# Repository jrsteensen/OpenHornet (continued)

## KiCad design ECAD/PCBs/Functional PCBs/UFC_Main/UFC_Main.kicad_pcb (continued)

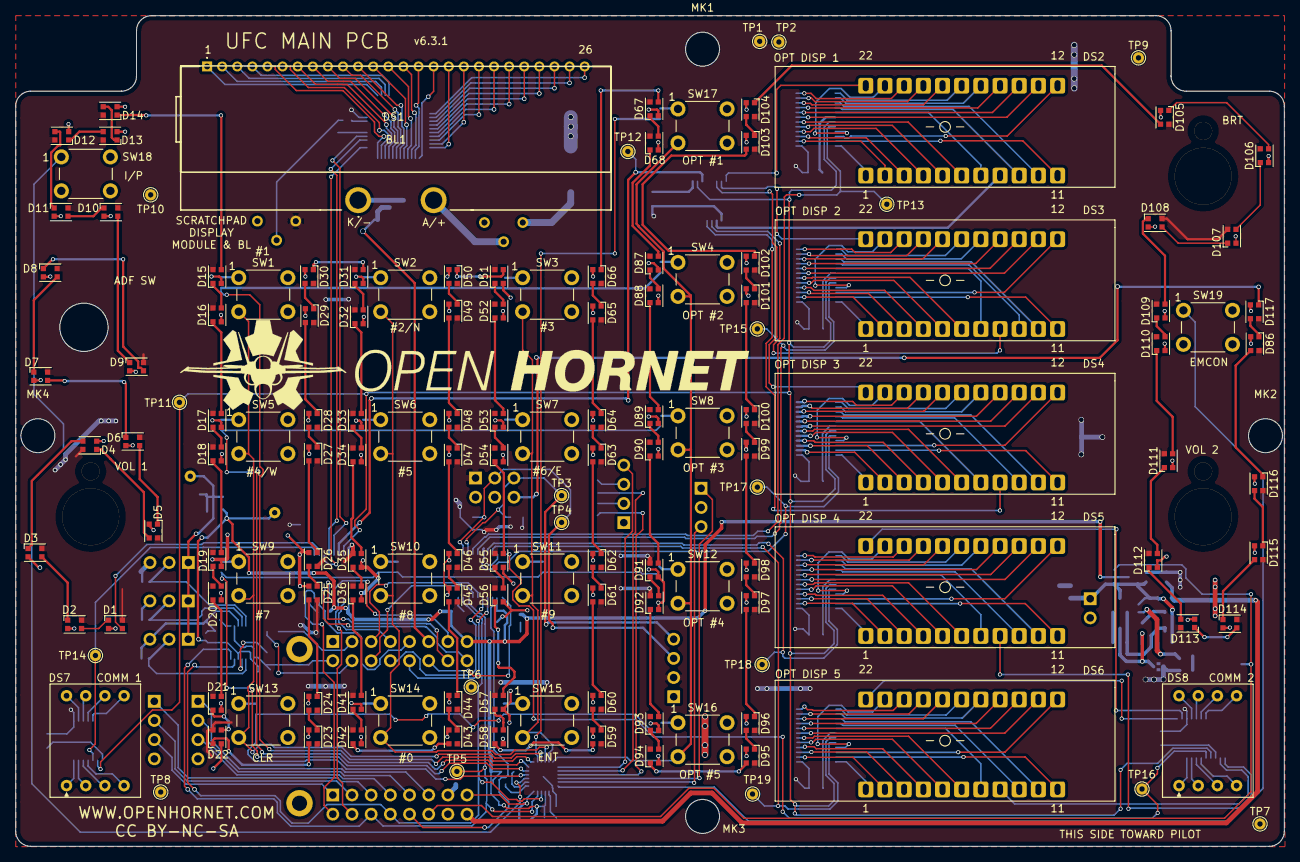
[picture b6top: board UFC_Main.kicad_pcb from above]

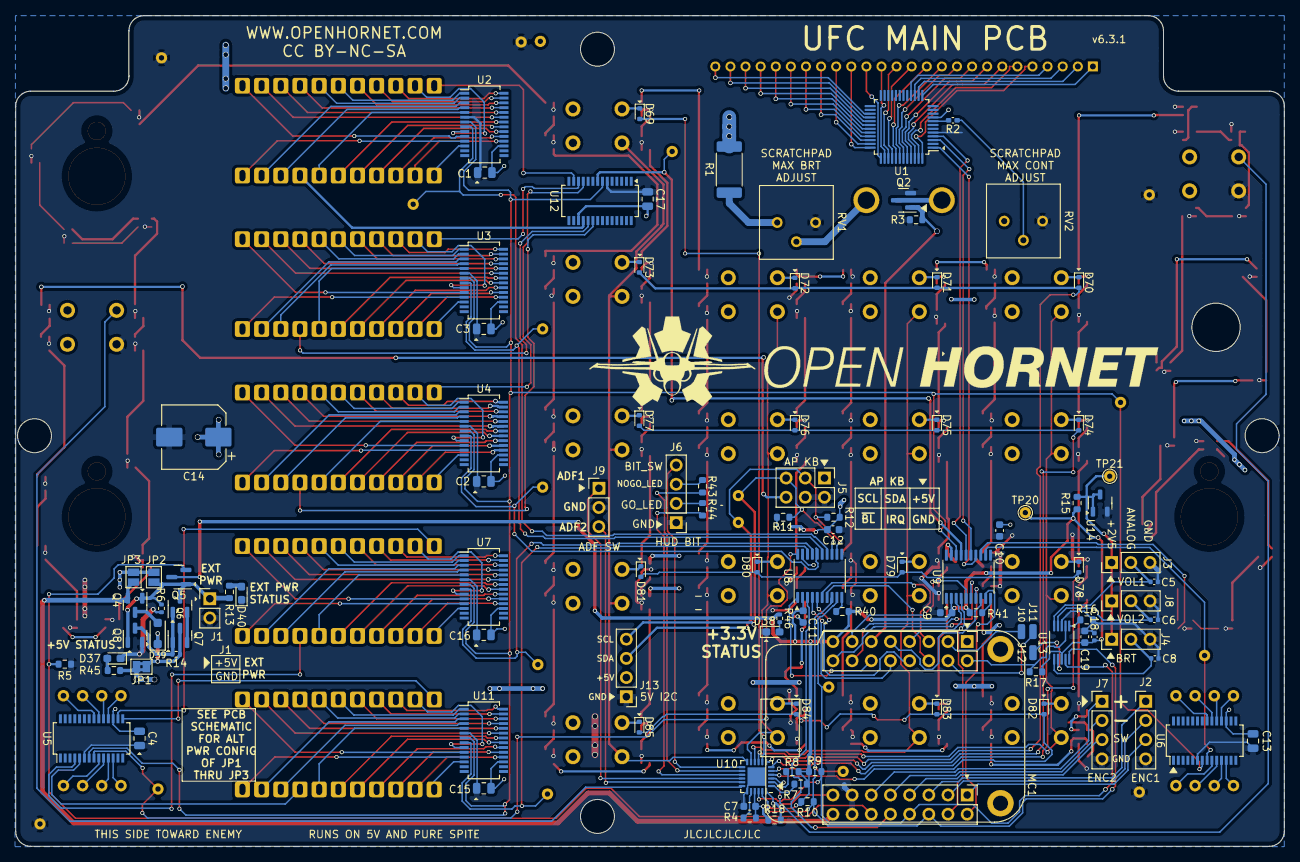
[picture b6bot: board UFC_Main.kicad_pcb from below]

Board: 2 copper layers, 168.0 x 110.0 mm, 257 parts (105 on the bottom side), 353 nets.

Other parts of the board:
LOGO: LOGO; LOGO_OH_Text_Large

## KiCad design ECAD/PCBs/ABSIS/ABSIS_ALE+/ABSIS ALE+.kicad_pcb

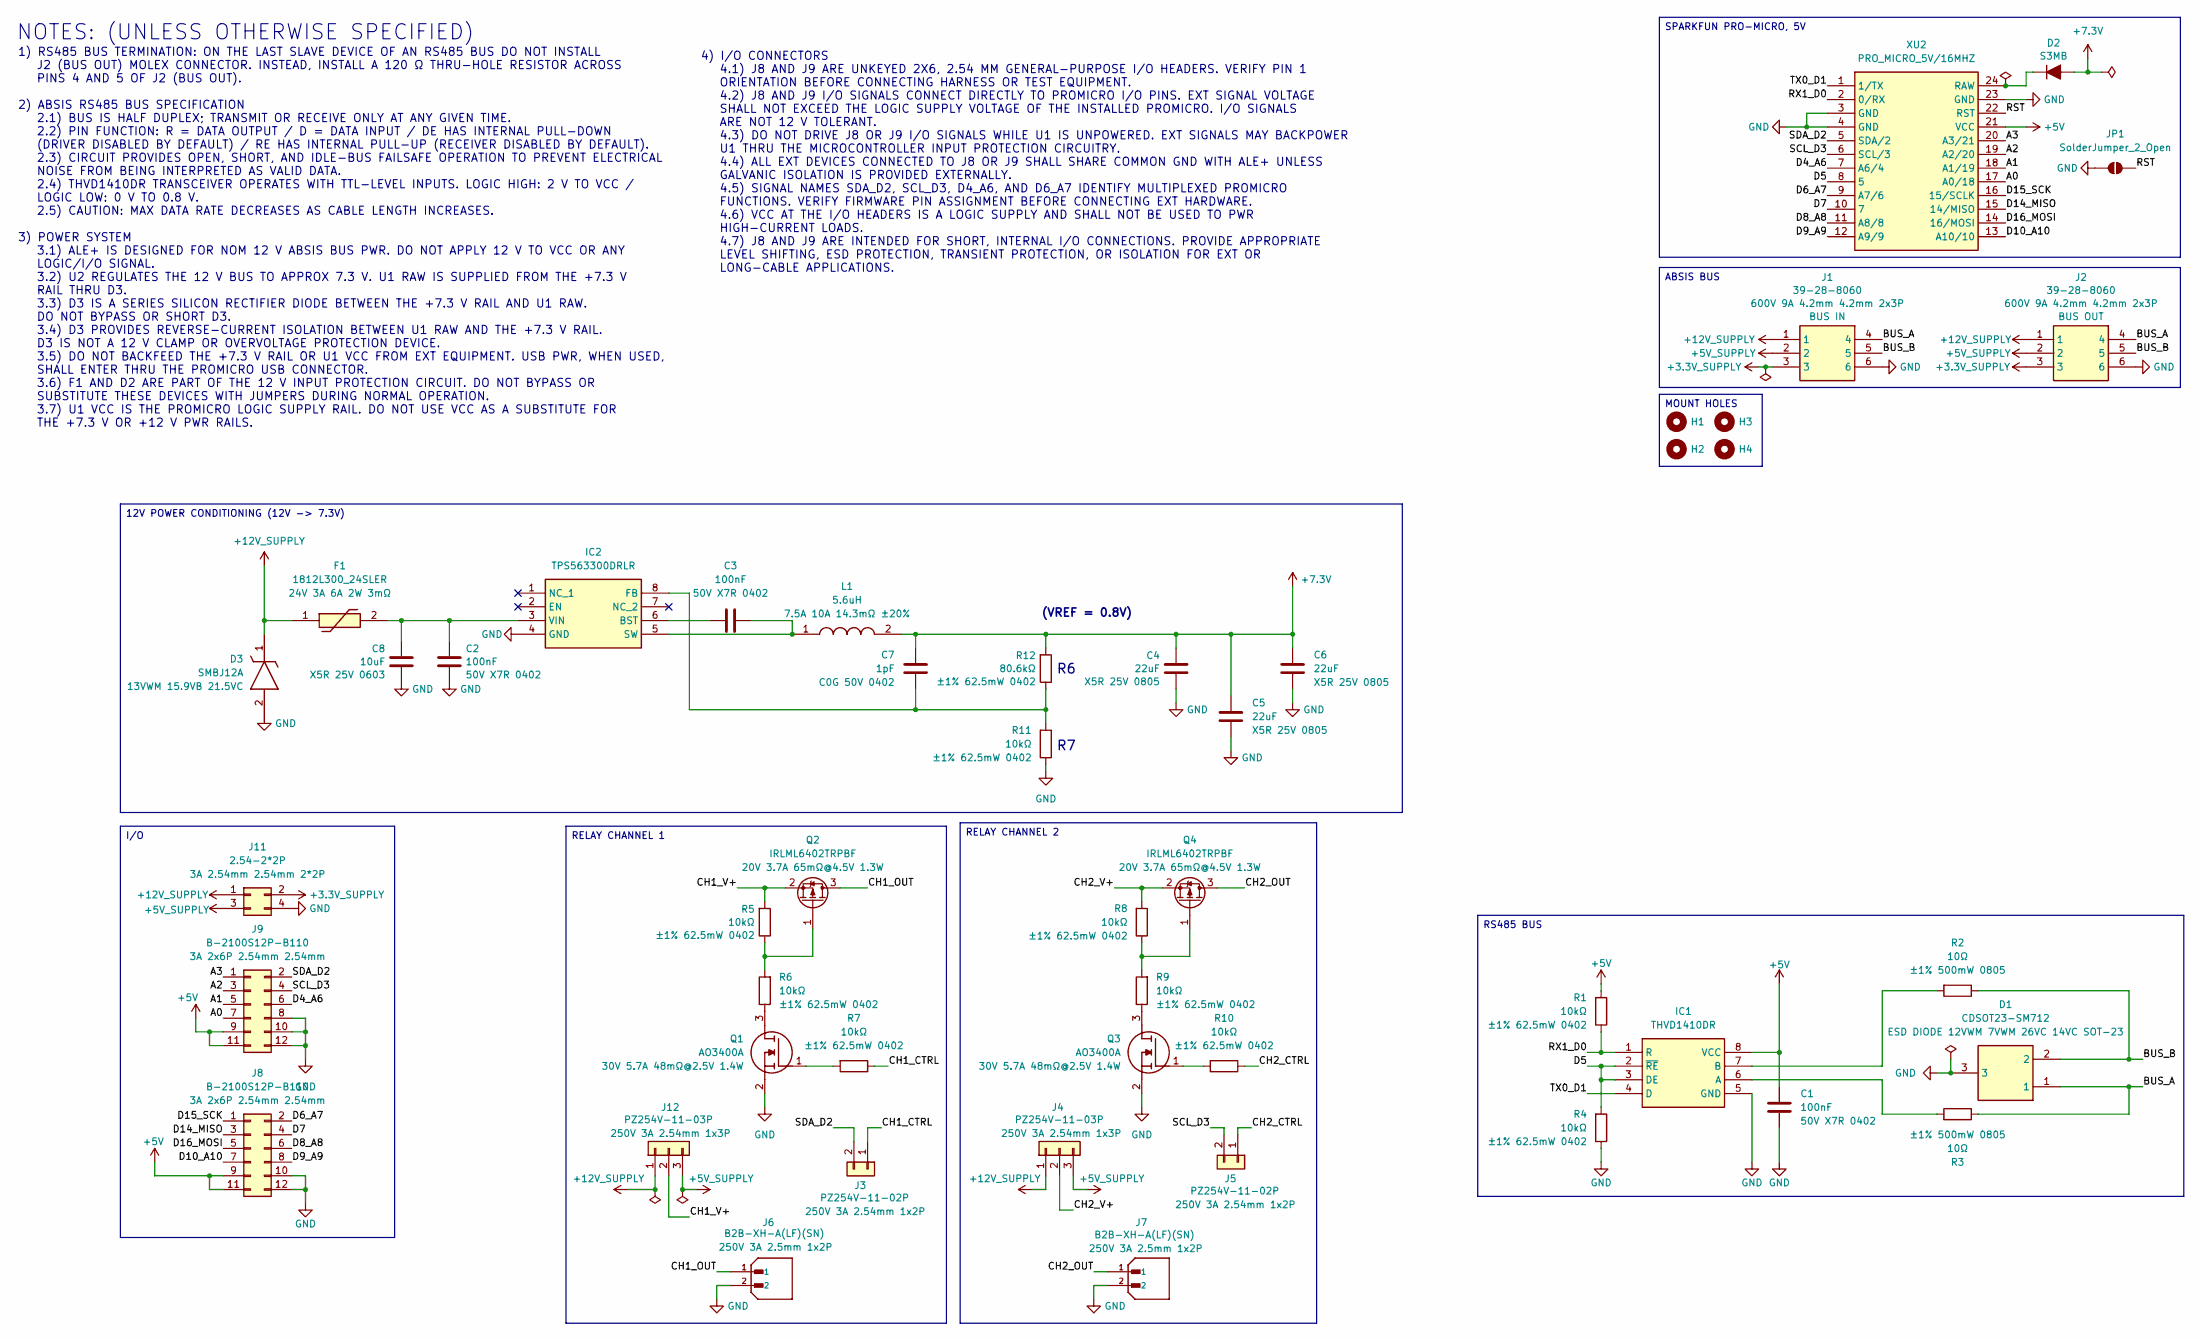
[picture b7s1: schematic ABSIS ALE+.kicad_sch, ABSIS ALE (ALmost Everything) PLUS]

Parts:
C1, C2, C3: 100nF; C_0402_1005Metric; Manufacturer PN CL05B104KB54PNC; LCSC C307331
C4, C5, C6: 22uF; C_0805_2012Metric; Manufacturer PN CL21A226MAQNNNE; LCSC C45783
C7: 1pF; C_0402_1005Metric; Manufacturer PN 0402CG1R0C500NT; LCSC C1550
C8: 10uF; C_0603_1608Metric; Manufacturer PN CL10A106MA8NRNC; LCSC C96446
D1: CDSOT23-SM712; Manufacturer PN CDSOT23-SM712; LCSC C404012
D2: S3MB; SS34; Manufacturer PN S3MB; LCSC C47524
D3: SMBJ12A; Manufacturer PN SMBJ12A; LCSC C151251
F1: 1812L300_24SLER; Manufacturer PN 1812L300/24SLER; LCSC C1512049
H1, H2, H3, H4: MountingHole; MountingHole_3.2mm_M3_DIN965
IC1: THVD1410DR; Manufacturer PN THVD1410DR; LCSC C2671345
IC2: TPS563300DRLR; Manufacturer PN TPS563300DRLR; LCSC C5219249
J1, J2: 39-28-8060; Manufacturer PN 39288060; LCSC C505058
J3, J5: PZ254V-11-02P; PinHeader_1x02_P2.54mm_Vertical; Manufacturer PN PZ254V-11-02P; LCSC C492401
J4, J12: PZ254V-11-03P; PinHeader_1x03_P2.54mm_Vertical; Manufacturer PN PZ254V-11-03P; LCSC C2937625
J6, J7: B2B-XH-A(LF)(SN); B2B-XH-A__LF__SN_; Manufacturer PN B2B-XH-A(LF)(SN); LCSC C158012
J8, J9: B-2100S12P-B110; PinHeader_2x06_P2.54mm_Vertical; Manufacturer PN B-2100S12P-B110; LCSC C124388
J11: 2.54-2*2P; PinHeader_2x02_P2.54mm_Vertical; Manufacturer PN 2.54-2*2P; LCSC C66690
JP1: SolderJumper_2_Open; SolderJumper-2_P1.3mm_Open_RoundedPad1.0x1.5mm
L1: 5.6uH; SRP6060FA-5R6M; Manufacturer PN SRP6060FA-5R6M; LCSC C1332221
Q1, Q3: AO3400A; Manufacturer PN AO3400A; LCSC C20917
Q2, Q4: IRLML6402TRPBF; Manufacturer PN IRLML6402TRPBF; LCSC C2593
R1, R4, R5, R6, R7, R8, R9, R10, R11: 10kΩ; R_0402_1005Metric; Manufacturer PN 0402WGF1002TCE; LCSC C25744
R2, R3: 10Ω; R_0805_2012Metric; Manufacturer PN CRCW080510R0FKEAHP; LCSC C844598
R12: 80.6kΩ; R_0402_1005Metric; Manufacturer PN 0402WGF8062TCE; LCSC C25921
XU2: PRO_MICRO_5V/16MHZ; PRO_MICRO_5V16MHZ; Manufacturer PN PRO_MICRO_5V/16MHZ

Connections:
+3.3V_SUPPLY: J1.3, J2.3, J11.2
+5V: C1.2, IC1.8 (VCC), J8.9, J8.11, J9.9, J9.11, R1.2, XU2.21 (VCC)
+5V_SUPPLY: J1.2, J2.2, J4.3, J11.3, J12.3
+7.3V: C4.1, C5.1, C6.1, C7.1, D2.2 (A), L1.2, R12.2
+12V_SUPPLY: D3.1 (K), F1.1, J1.1, J2.1, J4.1, J11.1, J12.1
/A0: J9.7, XU2.17 (A0/18)
/A1: J9.5, XU2.18 (A1/19)
/A2: J9.3, XU2.19 (A2/20)
/A3: J9.1, XU2.20 (A3/21)
/BUS_A: D1.1, J1.4, J2.4, R3.1
/BUS_B: D1.2, J1.5, J2.5, R2.1
/CH1_CTRL: J3.1, R7.1
/CH1_OUT: J6.1, Q2.3
/CH1_V+: J12.2, Q2.2, R5.2
/CH2_CTRL: J5.1, R10.1
/CH2_OUT: J7.1, Q4.3
/CH2_V+: J4.2, Q4.2, R8.2
/D4_A6: J9.6, XU2.7 (A6/4)
/D5: IC1.2 (~RE), IC1.3 (DE), R4.2, XU2.8 (5)
/D6_A7: J8.2, XU2.9 (A7/6)
/D7: J8.4, XU2.10 (7)
/D8_A8: J8.6, XU2.11 (A8/8)
/D9_A9: J8.8, XU2.12 (A9/9)
/D10_A10: J8.7, XU2.13 (A10/10)
/D14_MISO: J8.3, XU2.15 (14/MISO)
/D15_SCK: J8.1, XU2.16 (15/SCLK)
/D16_MOSI: J8.5, XU2.14 (16/MOSI)
/FB(TPS): C7.2, IC2.8 (FB), R11.2, R12.1
/RST: JP1.2 (B), XU2.22 (RST)
/RX1_D0: IC1.1 (R), R1.1, XU2.2 (0/RX)
/SCL_D3: J5.2, J9.4, XU2.6 (SCL/3)
/SDA_D2: J3.2, J9.2, XU2.5 (SDA/2)
/TX0_D1: IC1.4 (D), XU2.1 (1/TX)
GND: C1.1, C2.1, C4.2, C5.2, C6.2, C8.1, D1.3, D3.2 (A), IC1.5 (GND), IC2.4 (GND), J1.6, J2.6, J6.2, J7.2, J8.10, J8.12, J9.8, J9.10, J9.12, J11.4, JP1.1 (A), Q1.2 (S), Q3.2 (S), R4.1, R11.1, XU2.3 (GND), XU2.4 (GND), XU2.23 (GND)
unnamed: D2.1 (K), XU2.24 (RAW)
unnamed: IC1.6 (A), R3.2
unnamed: IC1.7 (B), R2.2
unnamed: C3.2, IC2.6 (BST)
unnamed: C3.1, IC2.5 (SW), L1.1
unnamed: C2.2, C8.2, F1.2, IC2.3 (VIN)
unnamed: Q1.3 (D), R6.1
unnamed: Q1.1 (G), R7.2
unnamed: Q2.1, R5.1, R6.2
unnamed: Q3.3 (D), R9.1
unnamed: Q3.1 (G), R10.2
unnamed: Q4.1, R8.1, R9.2

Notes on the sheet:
(VREF = 0.8V)
1) RS485 BUS TERMINATION: ON THE LAST SLAVE DEVICE OF AN RS485 BUS DO NOT INSTALL J2 (BUS OUT) MOLEX CONNECTOR. INSTEAD, INSTALL A 120 Ω THRU-HOLE RESISTOR ACROSS PINS 4 AND 5 OF J2 (BUS OUT). 2) ABSIS RS485 BUS SPECIFICATION 2.1) BUS IS HALF DUPLEX; TRANSMIT OR RECEIVE ONLY AT ANY GIVEN TIME. 2.2)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
4) I/O CONNECTORS 4.1) J8 AND J9 ARE UNKEYED 2X6, 2.54 MM GENERAL-PURPOSE I/O HEADERS. VERIFY PIN 1 ORIENTATION BEFORE CONNECTING HARNESS OR TEST EQUIPMENT. 4.2) J8 AND J9 I/O SIGNALS CONNECT DIRECTLY TO PROMICRO I/O PINS. EXT SIGNAL VOLTAGE SHALL NOT EXCEED THE LOGIC SUPPLY VOLTAGE OF THE INSTALLE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
NOTES: (UNLESS OTHERWISE SPECIFIED)
RELAY CHANNEL 2
MOUNT HOLES
RS485 BUS
RELAY CHANNEL 1
I/O
12V POWER CONDITIONING (12V -> 7.3V)
ABSIS BUS
SPARKFUN PRO-MICRO, 5V

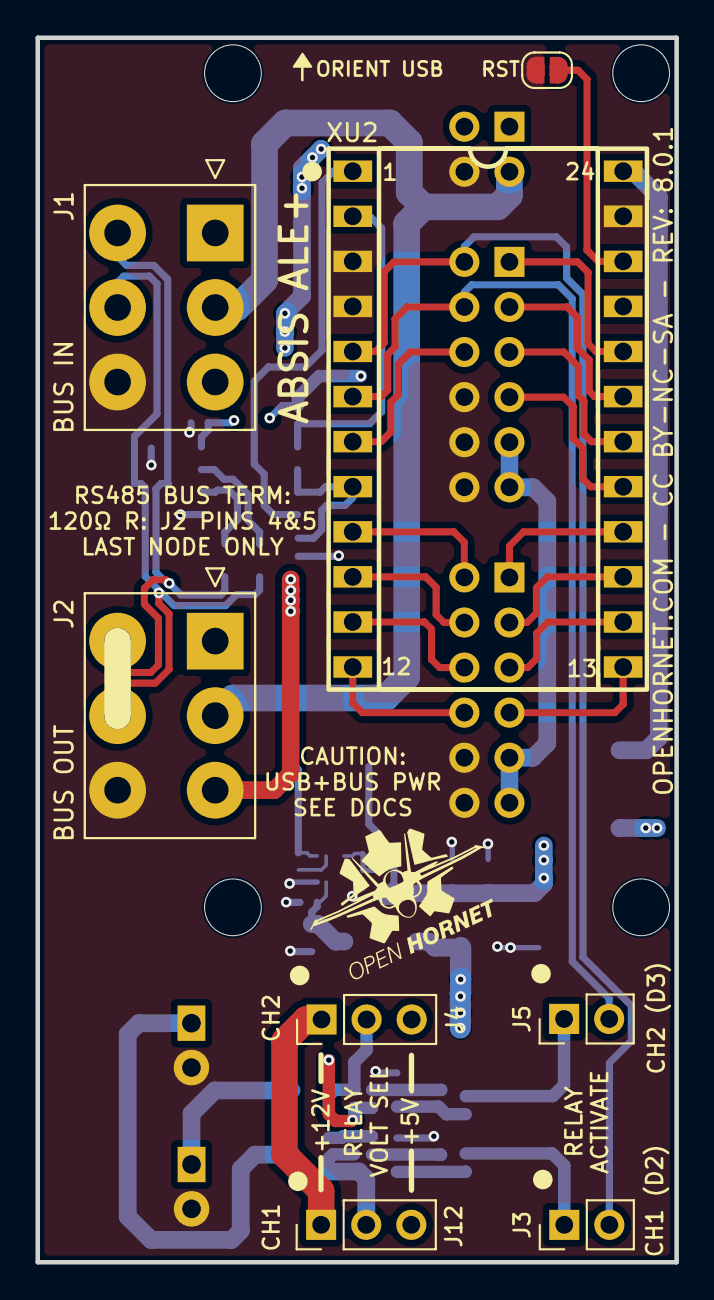
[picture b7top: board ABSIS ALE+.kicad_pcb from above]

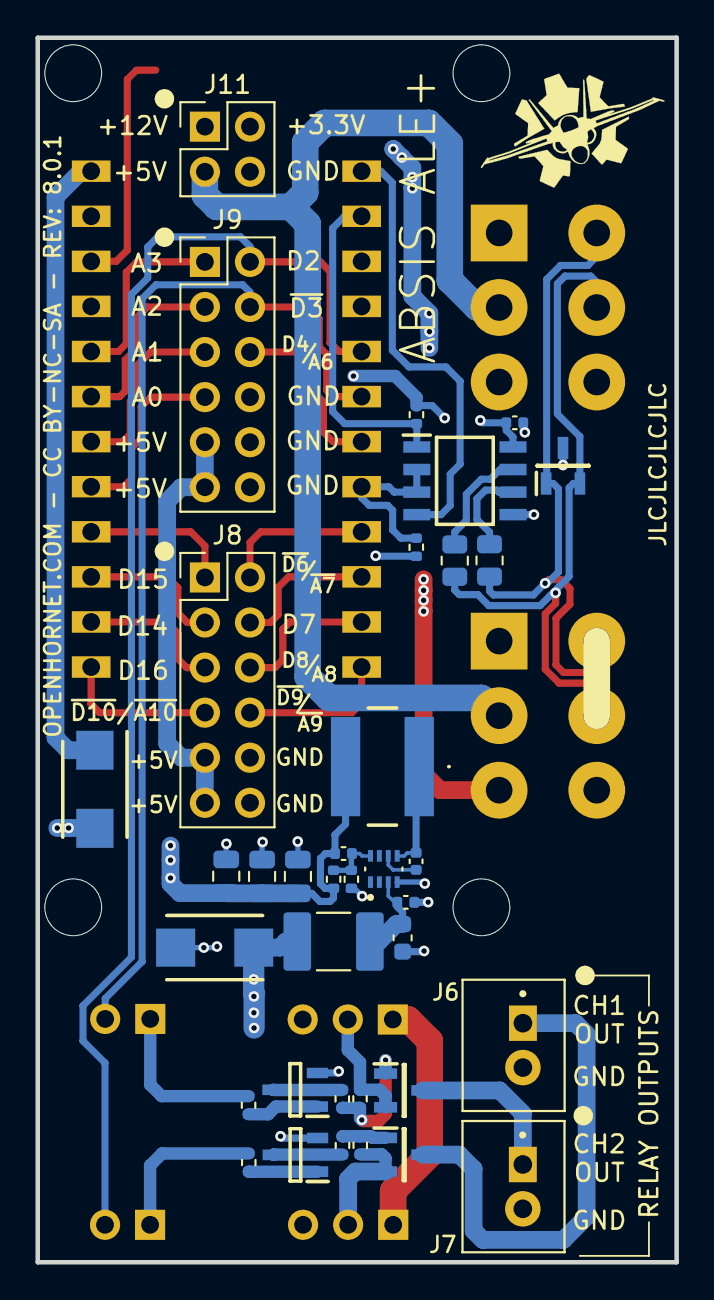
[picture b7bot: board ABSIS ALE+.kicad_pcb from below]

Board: 4 copper layers, 36.0 x 69.0 mm, 49 parts (37 on the bottom side), 46 nets.

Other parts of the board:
LOGO1: LOGO; LOGO_OH_NoText_Small

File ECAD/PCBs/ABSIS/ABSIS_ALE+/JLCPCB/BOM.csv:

"Reference","Qty","Value","DNP","Exclude from BOM","Exclude from Board","Footprint","Datasheet","LCSC","Manufacturer PN","Manufacturer_Name","Description"
"C1,C2,C3","3","100nF","","","","Capacitor_SMD:C_0402_1005Metric","https://www.lcsc.com/datasheet/C307331.pdf?spm=wm.sxq.inf.gg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","C307331","CL05B104KB54PNC","","50V X7R 0402"
"C4,C5,C6","3","22uF","","","","Capacitor_SMD:C_0805_2012Metric","https://www.lcsc.com/datasheet/C45783.pdf?spm=wm.sxq.inf.ggs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","C45783","CL21A226MAQNNNE","","X5R 25V 0805"
"C7","1","1pF","","","","Capacitor_SMD:C_0402_1005Metric","https://www.lcsc.com/datasheet/C1550.pdf?spm=wm.sxq.inf.ggs&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","C1550","0402CG1R0C500NT","","C0G 50V 0402"
"C8","1","10uF","","","","Capacitor_SMD:C_0603_1608Metric","https://www.lcsc.com/datasheet/C96446.pdf?spm=wm.sxq.inf.ggs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","C96446","CL10A106MA8NRNC","","X5R 25V 0603"
"D1","1","CDSOT23-SM712","","","","CDSOT23-SM712:CDSOT23-SM712","http://uk.rs-online.com/web/p/products/7673728","C404012","CDSOT23-SM712","","ESD DIODE 12VWM 7VWM 26VC 14VC SOT-23"
"D2","1","SS34","","","","SS34:SS34","https://datasheet.lcsc.com/szlcsc/MDD-Jiangsu-Yutai-Elec-SS3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","C8678","SS34","MDD(Microdiode Semiconductor)","Schottky Barrier Diodes (SBD) SMA(DO-214AC) RoHS"
"D3","1","SMBJ12A","","","","SMBJ12A:SMBJ12A","https://www.littelfuse.com/~/media/electronics/datasheets/tv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","C151251","SMBJ12A","LITTELFUSE","13VWM 15.9VB 21.5VC"
"F1","1","1812L300_24SLER","","","","1812L300_24SLER:1812L300_24SLER","https://www.littelfuse.com/~/media/electronics/datasheets/re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","C1512049","1812L300/24SLER ","LITTELFUSE","24V 3A 6A 2W 3mΩ"
"H1,H2,H3,H4","4","MountingHole","","Excluded from BOM","","MountingHole:MountingHole_3.2mm_M3_DIN965","~","","","","Mounting Hole without connection"
"IC1","1","THVD1410DR","","","","THVD1410DR:THVD1410DR","http://www.ti.com/lit/gpn/THVD1410","C2671345","THVD1410DR","","3.3-V to 5-V RS-485 transceiver with +/-18-kV IEC ESD protection"
"IC2","1","TPS563300DRLR","","","","TPS563300DRLR:TPS563300DRLR","https://www.ti.com/lit/ds/symlink/tps563300.pdf?ts=166603599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","C5219249","TPS563300DRLR","","TPS563300 3.8-V to 28-V, 3-A Synchronous Buck Converter in SOT583 Package"
"J1,J2","2","39-28-8060","","","","39288060:39-28-8060","https://www.molex.com/pdm_docs/sd/039281023_sd.pdf","C505058","39288060","MOLEX","600V 9A 4.2mm 4.2mm 2x3P"
"J3,J5","2","PZ254V-11-02P","","","","Connector_PinHeader_2.54mm:PinHeader_1x02_P2.54mm_Vertical","https://www.lcsc.com/datasheet/C492401.pdf?spm=wm.sxq.inf.gg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","C492401","PZ254V-11-02P","XFCN","250V 3A 2.54mm 1x2P"
"J4,J12","2","PZ254V-11-03P","","","","Connector_PinHeader_2.54mm:PinHeader_1x03_P2.54mm_Vertical","https://www.lcsc.com/datasheet/C2937625.pdf?spm=wm.sxq.inf.g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","C2937625","PZ254V-11-03P","PZ254V-11-03P,XFCN","250V 3A 2.54mm 1x3P"
"J6,J7","2","B2B-XH-A(LF)(SN)","","","","B2B-XH-A(LF)(SN):B2B-XH-A__LF__SN_","https://www.lcsc.com/datasheet/C158012.pdf?spm=wm.sxq.inf.gg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","C158012","B2B-XH-A(LF)(SN)","JST","250V 3A 2.5mm 1x2P"
"J8,J9","2","B-2100S12P-B110","","","","Connector_PinHeader_2.54mm:PinHeader_2x06_P2.54mm_Vertical","https://www.lcsc.com/datasheet/C124388.pdf?spm=wm.sxq.inf.gg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","C124388","B-2100S12P-B110","Ckmtw","3A 2x6P 2.54mm 2.54mm"
"J11","1","2.54-2*2P","","","","Connector_PinHeader_2.54mm:PinHeader_2x02_P2.54mm_Vertical","https://www.lcsc.com/datasheet/C66690.pdf?spm=wm.sxq.inf.ggs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","C66690","2.54-2*2P","","3A 2.54mm 2.54mm 2*2P"
"JP1","1","SolderJumper_2_Open","","Excluded from BOM","","Jumper:SolderJumper-2_P1.3mm_Open_RoundedPad1.0x1.5mm","~","","","","Solder Jumper, 2-pole, open"
"L1","1","5.6uH","","","","SRP6060FA-5R6M:SRP6060FA-5R6M","https://www.bourns.com/docs/Product-Datasheets/SRP6060FA.pdf","C1332221","SRP6060FA-5R6M","Bourns","7.5A 10A 14.3mΩ ±20%"
"Q1,Q3","2","AO3400A","","","","AO3400A:AO3400A","http://aosmd.com/res/data_sheets/AO3400A.pdf","C20917","AO3400A","","30V 5.7A 48mΩ@2.5V 1.4W"
"Q2,Q4","2","IRLML6402TRPBF","","","","IRLML6402TRPBF:IRLML6402TRPBF","http://www.infineon.com/dgdl/irlml6402pbf.pdf?fileId=5546d46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","C2593","IRLML6402TRPBF","","20V 3.7A 65mΩ@4.5V 1.3W"
"R1,R4,R5,R6,R7,R8,R9,R10,R11","9","10kΩ","","","","Resistor_SMD:R_0402_1005Metric","https://www.lcsc.com/datasheet/C25744.pdf?spm=wm.sxq.inf.ggs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","C25744","0402WGF1002TCE","","±1% 62.5mW 0402"
"R2,R3","2","10Ω","","","","Resistor_SMD:R_0805_2012Metric","https://www.lcsc.com/datasheet/C844598.pdf?spm=wm.sxq.inf.gg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","C844598","CRCW080510R0FKEAHP","","±1% 500mW 0805"
"R12","1","80.6kΩ","","","","Resistor_SMD:R_0402_1005Metric","https://www.lcsc.com/datasheet/C25921.pdf?spm=wm.sxq.inf.ggs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","C25921","0402WGF8062TCE","","±1% 62.5mW 0402"
"XU2","1","PRO_MICRO_5V/16MHZ","","","","PRO_MICRO_5V16MHZ:PRO_MICRO_5V16MHZ","https://cdn.sparkfun.com/assets/f/d/8/0/d/ProMicro16MHzv2.pdf","","PRO_MICRO_5V/16MHZ","","PRO MICRO ATMEGA32U4 5V/16MHZ"

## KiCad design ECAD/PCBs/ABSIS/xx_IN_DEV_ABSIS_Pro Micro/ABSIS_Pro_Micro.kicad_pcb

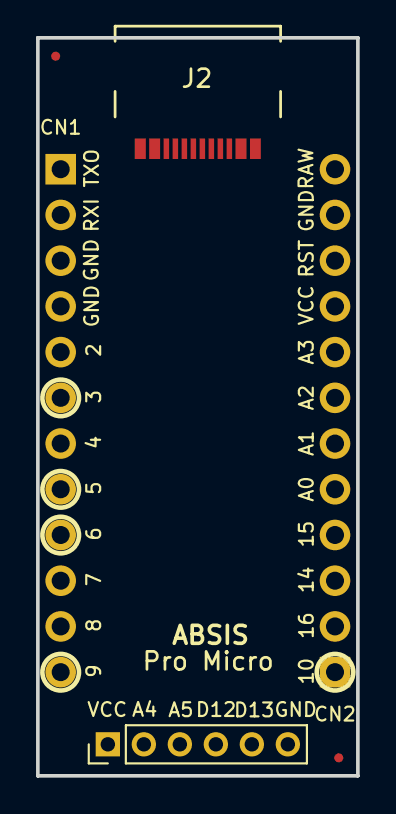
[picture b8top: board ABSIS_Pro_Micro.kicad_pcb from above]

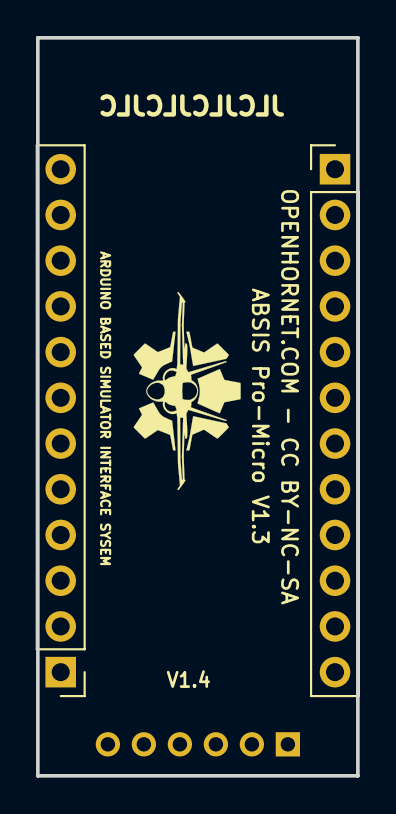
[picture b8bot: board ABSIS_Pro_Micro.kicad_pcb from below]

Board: 4 copper layers, 17.8 x 41.0 mm, 7 parts (3 on the bottom side), 5 nets, no tracks yet.

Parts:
CN1, CN2: M12PTH; PinHeader_1x12_P2.54mm_Vertical
CN3: PinHeader_1x06_P2.00mm_Vertical
F1: FIDUCIALUFIDUCIAL; Fiducial_0.5mm_Mask1.5mm
J2: 2171790001; 2171790001_MOL
JP3: FIDUCIALUFIDUCIAL; Fiducial_0.5mm_Mask1.5mm
LOGO: LOGO; LOGO_OH_NoText_Small

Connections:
+5V: CN2.9, CN3.1
/DN: J2.A7 (DN1), J2.B7 (DN2)
/DP: J2.A6 (DP1), J2.B6 (DP2)
/vBUS: J2.A4/B9 (VBUS), J2.B4/A9 (VBUS)
GND: CN1.3, CN1.4, CN2.11, CN3.6, J2.A1/B12 (GND), J2.B1/A12 (GND)

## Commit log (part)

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2024-10-19 UFC v6.2.0 (#1098)
    * Change to new TekCreations OPT Displays
    Updated schematic and PCB to integrate new TekCreations OPT display prototypes.
    Added new driver to drive independent cue digits of OPT 1 thru OPT 3
    Routed CUE digits of OPT 4 & 5 to COMM 2 driver.
    Replaced KB_INT with CUE_CLK
    Replaced 300ohm Scratchpad BL resistor with 10ohm with 1000ohm trimpot in series.
2024-10-19 Replaced knob.
    Replace SIM CNTL View Knob in MPL.
2024-10-20 Added alternate UFC button manufacturing files
    Added blank square and round buttons for UFC/AP, plus SVG legends for every button.
2024-10-20 Adding AMPCD User Mod (#1117)
    # OH2A3A1 AMPCD Modifications
    - **Author:** <A Hornet's Nest (Howling-Ape)>
    - **Contributed on:** <Oct 20, 2024>
    - **Derived from:** v<0.2.0>
    - **Original Assembly:** <OH2A3A1>
    ## Summary
2024-10-20 Deleted erroneous folder.
2024-11-28 Added one missing hole to face plate
2025-06-04 Add 12V USB injection
    Changed PCB size and add USB injection of 12V from ABSIS bus
2025-06-04 C5
    Add 2 missing connections
2025-08-29 revert to version without usb
    deleted both usb connectors and starting pcb design
2025-09-04 redraw zones
2025-09-04 line on the silkscreen removed...
2025-09-24 changed type of BOM and CPL file due jlcpcb import error
2025-10-05 Add test points for 3V3 and 2V5 rails
    Added TP20 (3V3) and TP21 (2V5) test points to the UFC_Main PCB and updated corresponding net segments. Also fixed minor silkscreen and code formatting issues in the PCB layout and schematic files. R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
2025-10-05 Update UFC_Main PCB BOM, CPL, and schematic
    Schematic notes updated to specify display package, and CPL/GERBER/PDF files regenerated to reflect these changes and copied to release folder.
2025-10-08 updated bom file
2025-10-09 Fix issue 1136, commit 1: Add tempfile to open draft PR
2025-10-19 Publish V3 of Ulus Winwing integration mod
2025-10-22 Added new version of HUD panel aft support
2025-11-02 Update ABSIS CABLES specification to v2
    Removed the previous version of the ABSIS CABLES specification PDF and added the updated v2 document which updated Type A and Type E cables to specify Twisted Stranded Pair for RS485 connections.
2025-12-09 Renaming and V3 improvements
2025-12-23 Add V4 of UFCOptionDigit
    updated pad to rectangular 2mm and a over 0.8x1.5mm drill
2025-12-30 Winwing integration V3.1 (#1189)
    * Add longeron cutout images to README.md. Add Glareshield with blisters contributed by Reaper021 and Bruce
    * Update README.md
2026-04-08 Updated UFC ADC/Pot circuit & replaced obsolete parts (#1171)
    * Add +2V5 reference and I2C header to UFC_Main PCB
    Introduced a +2V5 voltage reference circuit using ADR5040ARTZ and supporting components. Added a new 5V I2C pin header (J13). Updated net assignments and component placements to support the new refer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
    * Add test points for 3V3 and 2V5 rails
    Added TP20 (3V3) and TP21 (2V5) test points to the UFC_Main PCB and updated corresponding net segments. Also fixed minor silkscreen and code formatting issues in the PCB layout a
2026-04-08 Update README with new project information and links
    Updates for release
2026-04-08 Update copyright year in LICENSE.txt to 2026
2026-04-12 #1159 - Reverse orientation of Status LED
    Reversed orientation of D1 status LED
    Moved R1 to correct side of D1
    Assigned JLC PN to R1
    Updated R1 value to 120ohm
2026-04-16 Fix #1194 at APU panel: make space for hex nut at ENG crank switch
2026-04-18 Added Canopy Bow
2026-04-27 Update OH4A3A1-100 - ASSY, SELECT JETT SWITCH MECH Drawing v12.pdf
    REV A APPEARS IN TITLE BLOCK.
    ENTIRE DRAWING SUBMITTED
    REVISION HISTORY TABLE ONLY APPEARS ON SHEET 1 OF DRAWING
    REVISION HISTORY DESCRIPTION OF REV A REVISED TO: "-106 MAKE FROM WAS: 9056K64; IS: 9056K62"
2026-04-27 Changes before error encountered
    Agent-Logs-Url: https://github.com/jrsteensen/OpenHornet/sessions/f3b37839-1fa4-40a7-a4a8-77c9f97733bf
2026-04-27 Address PR #1209 review comments: PNG lossless, alpha docs, pinned deps, pip3, fork guard, comment resilience, README sync
    Agent-Logs-Url: https://github.com/jrsteensen/OpenHornet/sessions/259371e1-9559-4a6b-a993-d781e51bee22
2026-04-27 Fix Pillow vulnerabilities: bump pin from 10.3.0 to 12.2.0
    Agent-Logs-Url: https://github.com/jrsteensen/OpenHornet/sessions/259371e1-9559-4a6b-a993-d781e51bee22
2026-04-28 Bump actions/checkout to v6 and actions/upload-artifact to v7 for Node.js 24 support
    Agent-Logs-Url: https://github.com/jrsteensen/OpenHornet/sessions/9b1651b1-c1ef-4b98-8625-61d148272718
2026-04-28 feat: detect and flag malformed PDF names in overlay compare workflow
    - make_key() now uses regex ^([A-Za-z0-9-]+) to extract the part-number
    key from the filename stem, handling both well-formed separators (_)
    and malformed ones (space, dash, comma, etc.)
    e.g. "OH4A1A1-1 - ASSY, LEFT CONSOLE STRUCTURE v7.pdf" → key "OH4A1A1-1"
    - Add is_malformed() helper: True when the character after the key is not _
    - Track malformed_new in pair records and malformed_added in skipped records
2026-04-28 feat: add WAS/OLD (red) and IS/NEW (green) label strip to each comparison PDF page
    Agent-Logs-Url: https://github.com/jrsteensen/OpenHornet/sessions/cace1a88-c8e1-435c-994f-af0e601644d9
2026-04-28 Fix: Pin PyMuPDF to wheel-only version and set Python 3.11 in PDF Overlay Compare workflow
    Agent-Logs-Url: https://github.com/jrsteensen/OpenHornet/sessions/6b4d9fb6-d1c6-42f5-9cee-89bb8bfc062d
2026-04-28 Remove v11 PDF and rename v12 drawing
    Delete obsolete OH4A3A1-100 v11 PDF and rename the v12 drawing file to a standardized filename in release/OH4_Left_Console. The v12 file content is unchanged (100% similarity); only the filename was 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
2026-04-30 Corrected the drawing.
    Corrected the parts alignment on page 1
2026-05-01 Redline updates to Left Console Structure drawings
2026-05-01 Redlines resolves and file namings updated
2026-05-02 Update to FN ordering
    Fixed FN ordering caused by adding new screw to the model. Screw was added to the middle of the parts list incrementing all the parts after its addition by one. New screw is now FN57. FN58 I could no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
2026-05-02 Clarify jumper instructions and rework nets
    Replace the solder-jumper note with explicit, safety-focused instructions for JP1/JP2/JP3 and reposition that text. Large tidy-up of schematic nets: many junctions, wires and labels were repositioned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
2026-05-03 Commit for Development Version of the ABSIS_Pro Micro
    design notes and requirement.
    JLCPCB Parts Identified, Datasheets for each part attached
    needs to be routed
    notes for routing are in the PCB file
2026-05-03 Updated file names issue #1138
    RMRK_BLACK files names addressed in issue are already corrected. Changed 10 file names from RMRK_.005 to ACRL_.005
2026-05-07 Add Fusion 360 + rotary switch/stepper tutorials
    Add three new tutorials: converting a bleed-air rotary switch to 360° travel, modifying VID29-02P gauge steppers for continuous travel, and instructions for downloading/importing OpenHornet Fusion 36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
2026-05-08 Add v0.3.0 option to feature request template
2026-05-21 Updated manufacturing file
    This is the updated manufacturing file the upper mount.
2026-05-21 Updated LIP structure drawing
    This is the updated LIP structure drawing.
2026-05-22 Updated Manufacturing file
    This is the update .3mf manufacturing file.
2026-05-22 Changes to BOM
    Added 5 panhead screws (91249A146) and removed 5 panhead screws (91249A148).
2026-05-23 Updated changes to Dimension positioning
    Updated changes to the positioning of the additional dimensions added to the landing gear lever shaft.
2026-05-23 Deletion of incorrect drawing files
    Deleted incorrect version files.
2026-05-23 Updated to correct file version
    Update drawing file to correct version (V28)
2026-05-24 Delete OH2A1A1-1 - ASSY, LOWER INSTRUMENT PANEL STRUCTURE_A_v12.pdf
    Deleted old file
2026-05-24 FIX: #1057 - Recessed ECM Backplate on LIP to fit flush with LIP Faceplate (#1226)
    * Lower Instrument Assy Drawing Change
    Lower Instrument Assy Drawing changes
    * Updated Manufacturing file
    This is the update .3mf manufacturing file.
    * Changes to the drawing REV number
    The REV number was changed to REV A
2026-05-24 Update donate link in ECAD docs
    Replace outdated donate URL (/campaigns/donate/) with the new /donate.html in ECAD/README.md and ECAD/MANUFACTURING.md to point users to the correct donation page.
2026-05-24 Dispatch docs deployment on hardware documentation changes
2026-05-24 Skip docs dispatch when token is unavailable
2026-05-24 Update to the LDG Gear shaft drawing.
    Update dimension layout on the LDG gear shaft drawing.
2026-05-25 FIX: Added dimensions to gear lever shaft drawing (#1227)
    * Added dimensions to gear lever shaft drawing
    Added additional dimensions in the drawing on landing gear lever shaft to help with manufacturing.
    * Updated changes to Dimension positioning
    Updated changes to the positioning of the additional dimensions added to the landing gear lever shaft.
    * Update to the LDG Gear shaft drawing.
    Update dimension layout on the LDG gear shaft drawing.
2026-05-25 Update README and Doxyfile project metadata
    Add a top-level TOC header to README. Simplify Doxyfile project metadata by renaming PROJECT_NAME to Hardware Documentation and clearing PROJECT_BRIEF (removing OpenHornet-specific text). Also enable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
2026-05-28 Initial commit for ABSIS Bus Master and Mega
    This is the initial commit for the ABSIS Bus Master and Mega as received from contractor. Do not use yet until PR is merged.
2026-05-29 Add RS485 drain screw terminal symbol and J6
    Add a Screw_Terminal_01x01 schematic symbol and place a J6 instance for the RS485 drain on the ABSIS_Bus_Master schematic. Includes footprint (Wuerth REDCUBE THR 74650073), manufacturer PN, datasheet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
2026-05-29 General ECAD cleanup
    Moved original OH design to legacy folder
    Moved externally provided library symbols, footprints, and STEP files to appropriate OH library locations.
    Upgraded project to KiCAD 10
    Removed production files from ABSIS Pro_Micro since it is not yet production ready.
2026-05-29 PCB Updates
    Made all components display 3D models
    Updated silkscreens
    Added RS485 Drain Screw Terminal to PCB
    Also add new 3D model file ECAD/lib/OH_3DModels/360272.stp.
2026-05-30 ABSIS_Mega: Started schematic cleanup
2026-06-05 Bump PCB revision to 6.0.0 and regenerate outputs
    Update ABSIS_Bus_Master revision to 6.0.0 and regenerate all derived outputs. This commit updates ABSIS_Bus_Master.kicad_pcb (rev/date), refreshes Gerber layers (ProjectId/CreationDate and some layou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
2026-06-06 Renamed ABSIS Mega folder
2026-06-07 Change wingfold detent orientation (#1230)
    Changes to the orientation of the wingfold detent shaft blocks and handle. No physical changes to any parts or parts list.
2026-06-08 Update KiCad footprints and ProMicro symbol
    Refresh two OH footprints and adjust the Pro Micro symbol layout. In footprints (CDSOT23-SM712, THVD1410DR) many element UUIDs were regenerated and 3D model paths were changed to use ${KICAD_USER_OH_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
2026-06-24 Change AMPCD PCB material code and part description (#1231)
    Change the material code from PETG to N/A and add PCB to the part description. Fixes #1224.
